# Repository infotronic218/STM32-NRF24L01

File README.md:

# STM32-NRF24L01
Designing NRF24L01 circuit with an STM32 MCU
The design was inspired from Phil Lab (Youtube channel) video. I reproduce his work in order to learn more 
about RF circuit PCB layout.

# 3D View of the board

# PCB Layout

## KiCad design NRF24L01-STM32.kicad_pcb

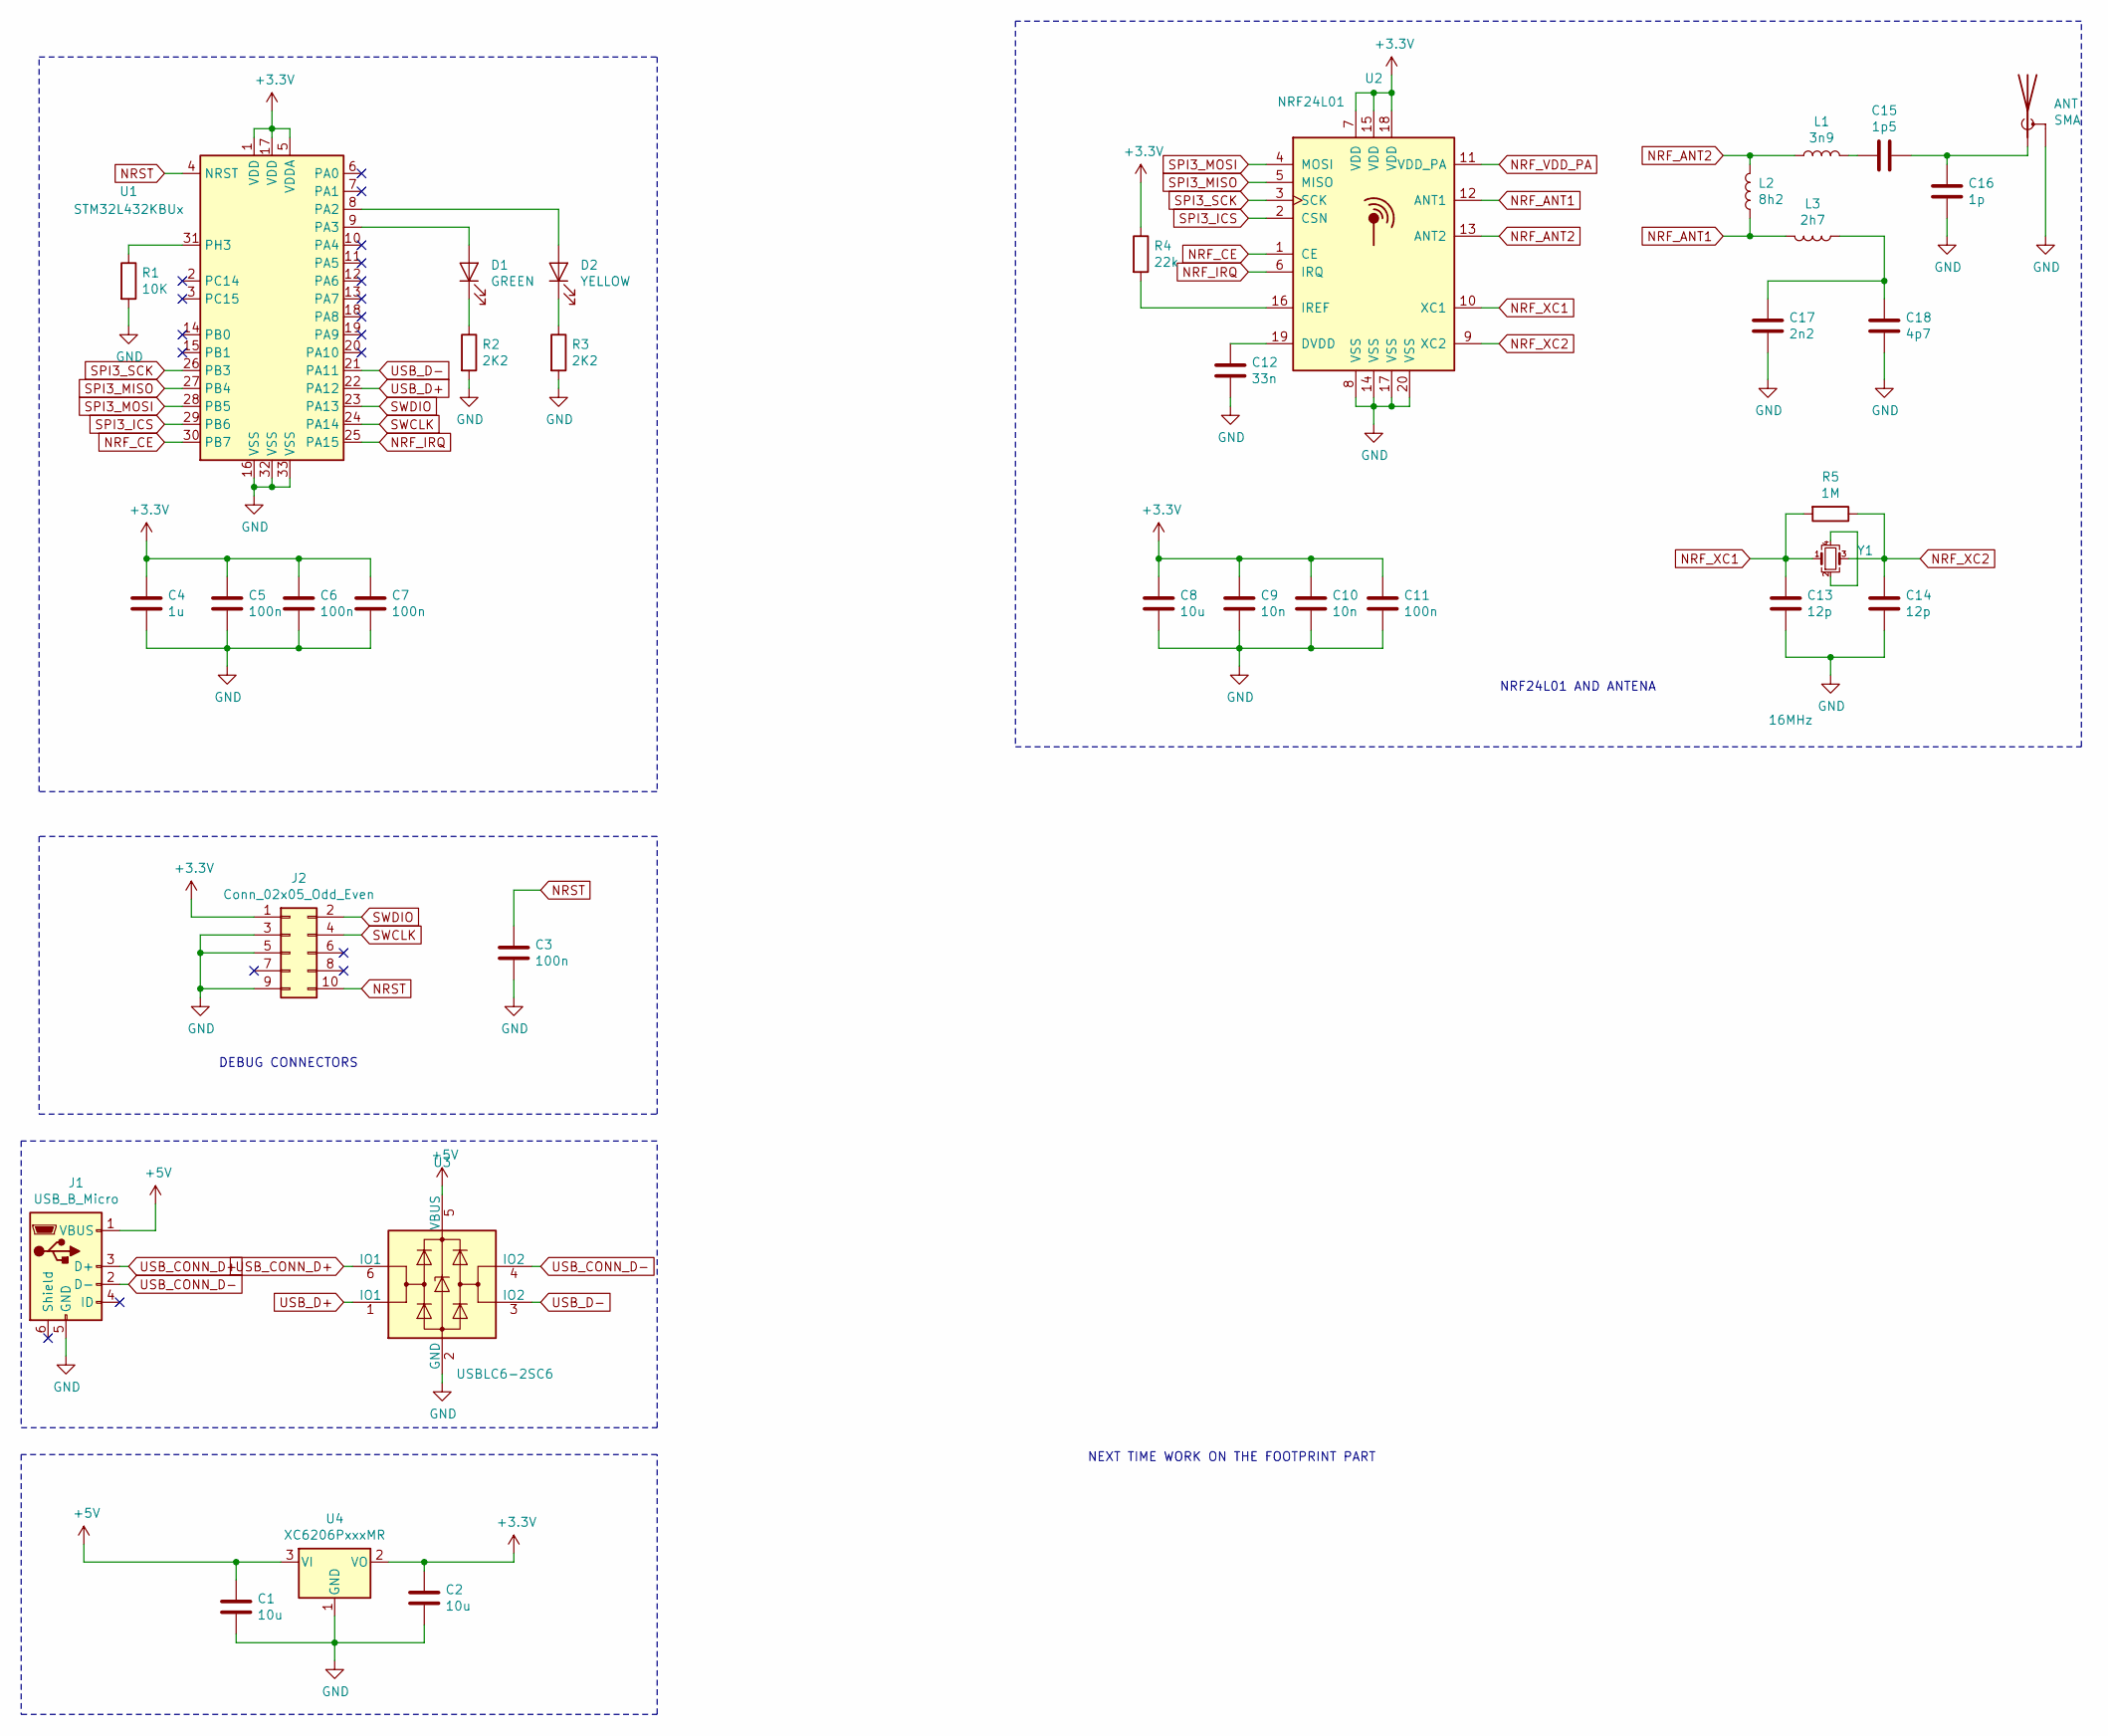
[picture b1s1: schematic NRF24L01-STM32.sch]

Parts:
ANT: SMA; SMA_Samtec_SMA-J-P-X-ST-EM1_EdgeMount
C1, C2, C8: 10u; C_0603_1608Metric
C3, C5, C6, C7, C11: 100n; C_0402_1005Metric
C4: 1u; C_0402_1005Metric
C9, C10: 10n; C_0402_1005Metric
C12: 33n; C_0402_1005Metric
C13, C14: 12p; C_0402_1005Metric
C15: 1p5; C_0402_1005Metric
C16: 1p; C_0402_1005Metric
C17: 2n2; C_0402_1005Metric
C18: 4p7; C_0402_1005Metric
D1: GREEN; LED_0603_1608Metric_Pad1.05x0.95mm_HandSolder
D2: YELLOW; LED_0603_1608Metric_Pad1.05x0.95mm_HandSolder
J1: USB_B_Micro; USB_Micro-B_Molex-105017-0001
J2: Conn_02x05_Odd_Even; PinHeader_2x05_P1.27mm_Vertical
L1: 3n9; L_0402_1005Metric
L2: 8h2; L_0402_1005Metric
L3: 2h7; L_0402_1005Metric
R1: 10K; R_0402_1005Metric
R2, R3: 2K2; R_0603_1608Metric
R4: 22k; R_0402_1005Metric
R5: 1M; R_0402_1005Metric
U1: STM32L432KBUx; QFN-32-1EP_5x5mm_P0.5mm_EP3.45x3.45mm
U2: NRF24L01; QFN-20-1EP_4x4mm_P0.5mm_EP2.5x2.5mm
U3: USBLC6-2SC6; SOT-23-6
U4: XC6206PxxxMR; SOT-23
Y1: 16MHz; Crystal_SMD_3225-4Pin_3.2x2.5mm

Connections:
+3V3: C2.1, C4.1, C5.1, C6.1, C7.1, C8.1, C9.1, C10.1, C11.1, J2.1, R4.1, U1.1 (VDD), U1.5 (VDDA), U1.17 (VDD), U2.7 (VDD), U2.15 (VDD), U2.18 (VDD), U4.2 (VO)
+5V: C1.1, J1.1 (VBUS), U3.5 (VBUS), U4.3 (VI)
GND: ANT.2 (Shield), C1.2, C2.2, C3.2, C4.2, C5.2, C6.2, C7.2, C8.2, C9.2, C10.2, C11.2, C12.2, C13.2, C14.2, C16.2, C17.2, C18.2, J1.5 (GND), J2.3, J2.5, J2.9, R1.2, R2.2, R3.2, U1.16 (VSS), U1.32 (VSS), U1.33 (VSS), U2.8 (VSS), U2.14 (VSS), U2.17 (VSS), U2.20 (VSS), U3.2 (GND), U4.1 (GND); also elsewhere on the board
NRF_ANT1: L2.1, L3.2, U2.12 (ANT1)
NRF_ANT2: L1.1, L2.2, U2.13 (ANT2)
NRF_CE: U1.30 (PB7), U2.1 (CE)
NRF_IRQ: U1.25 (PA15), U2.6 (IRQ)
NRF_XC1: C13.1, R5.2, U2.10 (XC1), Y1.1
NRF_XC2: C14.1, R5.1, U2.9 (XC2), Y1.3
NRST: C3.1, J2.10, U1.4 (NRST)
unnamed 10: ANT.1 (A), C15.1, C16.1; also elsewhere on the board
unnamed: C12.1, U2.19 (DVDD)
unnamed: C15.2, L1.2
unnamed: C17.1, C18.1, L3.1
unnamed 14: D1.1 (K), R2.1; also elsewhere on the board
unnamed 15: D1.2 (A), U1.9 (PA3); also elsewhere on the board
unnamed 16: D2.1 (K), R3.1; also elsewhere on the board
unnamed 17: D2.2 (A), U1.8 (PA2); also elsewhere on the board
unnamed: R1.1, U1.31 (PH3)
unnamed: R4.2, U2.16 (IREF)
unnamed: Y1.2, Y1.4
SPI3_ICS: U1.29 (PB6), U2.2 (CSN)
SPI3_MISO: U1.27 (PB4), U2.5 (MISO)
SPI3_MOSI: U1.28 (PB5), U2.4 (MOSI)
SPI3_SCK: U1.26 (PB3), U2.3 (SCK)
SWCLK: J2.4, U1.24 (PA14)
SWDIO: J2.2, U1.23 (PA13)
USB_CONN_D+: J1.3 (D+), U3.6 (IO1)
USB_CONN_D-: J1.2 (D-), U3.4 (IO2)
USB_D+: U1.22 (PA12), U3.1 (IO1)
USB_D-: U1.21 (PA11), U3.3 (IO2)

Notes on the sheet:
DEBUG CONNECTORS
NRF24L01 AND ANTENA
NEXT TIME WORK ON THE FOOTPRINT PART

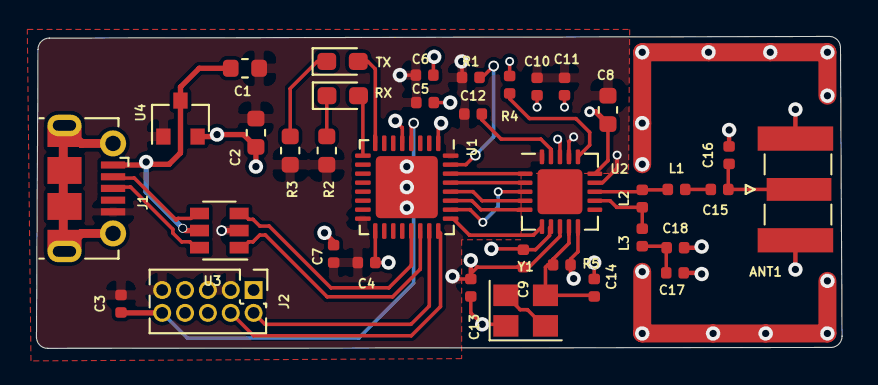
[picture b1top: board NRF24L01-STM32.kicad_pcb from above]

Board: 4 copper layers, 44.8 x 17.3 mm, 36 parts (0 on the bottom side), 31 nets.

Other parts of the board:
ANT1: SMA; SMA_Samtec_SMA-J-P-X-ST-EM1_EdgeMount
RX: GREEN; LED_0603_1608Metric_Pad1.05x0.95mm_HandSolder
TX: YELLOW; LED_0603_1608Metric_Pad1.05x0.95mm_HandSolder

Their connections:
GND: ANT1.2; also elsewhere on the board
unnamed 10: ANT1.1; also elsewhere on the board
unnamed 14: RX.1; also elsewhere on the board
unnamed 15: RX.2; also elsewhere on the board
unnamed 16: TX.1; also elsewhere on the board
unnamed 17: TX.2; also elsewhere on the board

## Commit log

2021-01-04 Update images
